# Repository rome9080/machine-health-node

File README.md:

# Industrial Machine Health Node

A 4-layer PCB that monitors the health of a machine (motor, pump, fan) by analysing vibration and motor current on-device. An FPGA running my own RISC-V CPU does the processing, and results go out over BLE, RS-485 (Modbus) or USB to a small software stack.

Full scope, parts, add-ons and phases are in [docs/PROJECT_PLAN.md](docs/PROJECT_PLAN.md). Design decisions are logged in [DESIGN_LOG.md](DESIGN_LOG.md).

## Highlights

- 4-layer board: AMD Spartan-7 FPGA (BGA), multi-rail power from a 9 to 36 V input, USB, RS-485, CAN FD
- Runs my own 32-bit RISC-V core (see [riscv-cpu](https://github.com/rome9080/riscv-cpu))
- Vibration and motor-current analysis on the device
- Add-ons: signal integrity, design for manufacture, bare-metal C toolchain, edge ML, telemetry dashboard, CI pipeline, requirements traceability

## Status

| Phase | State |
|-------|-------|
| 0. Scope and plan | Done |
| 1. Architecture and part selection | Done (final BOM costing happens in Phase 4) |
| 2. Schematic | Next |
| 3. Layout | Not started |
| 4. Fabrication | Not started |
| 5. RTL, firmware, software | Not started |
| 6. Bring-up | Not started |
| 7. Testing and write-up | Not started |

## Repository layout

- `docs/PROJECT_PLAN.md`: scope, add-ons, phases, risks
- `DESIGN_LOG.md`: decision log
- `docs/archive/`: the earlier 2-layer sensor-node concept
- Hardware, RTL, firmware and software folders will be added as each phase starts

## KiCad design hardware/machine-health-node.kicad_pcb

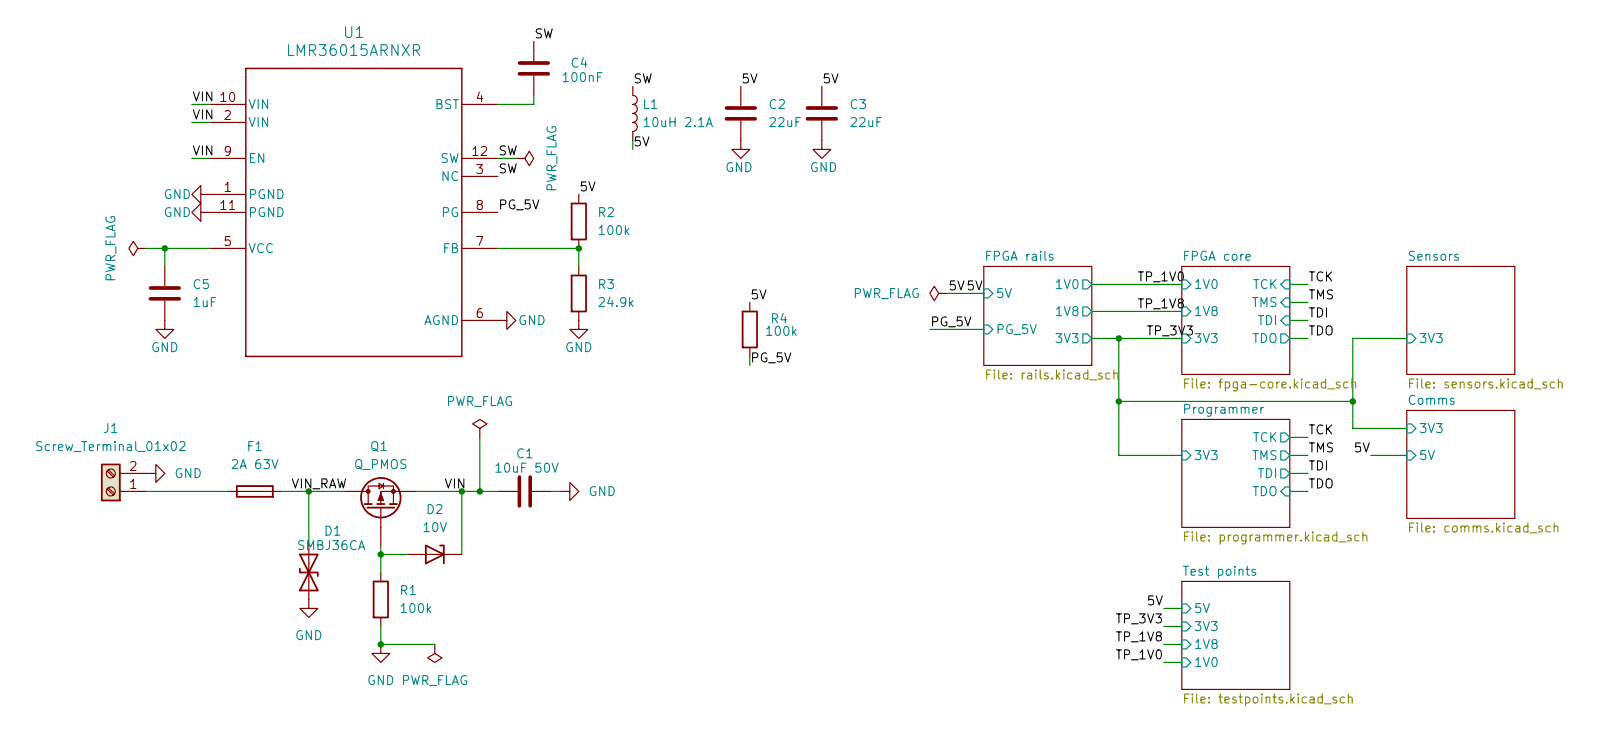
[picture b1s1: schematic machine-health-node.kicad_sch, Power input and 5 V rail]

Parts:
C1: 10uF 50V; C_1206_3216Metric
C2, C3: 22uF; C_0805_2012Metric
C4: 100nF; C_0402_1005Metric
C5: 1uF; C_0402_1005Metric
D1: SMBJ36CA; D_SMB
D2: 10V; D_SOD-123
F1: 2A 63V; Fuse_1206_3216Metric
J1: Screw_Terminal_01x02; TerminalBlock_Phoenix_MKDS-1,5-2-5.08_1x02_P5.08mm_Horizont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
L1: 10uH 2.1A; L_Taiyo-Yuden_NR-50xx
Q1: Q_PMOS; SOT-23
R1, R2, R4: 100k; R_0402_1005Metric
R3: 24.9k; R_0402_1005Metric
U1: LMR36015ARNXR; RNX0012B

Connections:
/5V: C2.1, C3.1, L1.2, R2.1, R4.1; also elsewhere on the board
/PG_5V: R4.2, U1.8 (PG); also elsewhere on the board
/SW: C4.1, L1.1, U1.3 (NC), U1.12 (SW)
/VIN: C1.1, D2.1 (K), Q1.2 (S), U1.2 (VIN), U1.9 (EN), U1.10 (VIN)
/VIN_RAW: D1.2 (A2), F1.2, Q1.3 (D)
GND: C1.2, C2.2, C3.2, C5.2, D1.1 (A1), J1.2, R1.2, R3.2, U1.1 (PGND), U1.6 (AGND), U1.11 (PGND); also elsewhere on the board
unnamed: D2.2 (A), Q1.1 (G), R1.1
unnamed: F1.1, J1.1
unnamed: C4.2, U1.4 (BST)
unnamed: R2.2, R3.1, U1.7 (FB)
unnamed: C5.1, U1.5 (VCC)

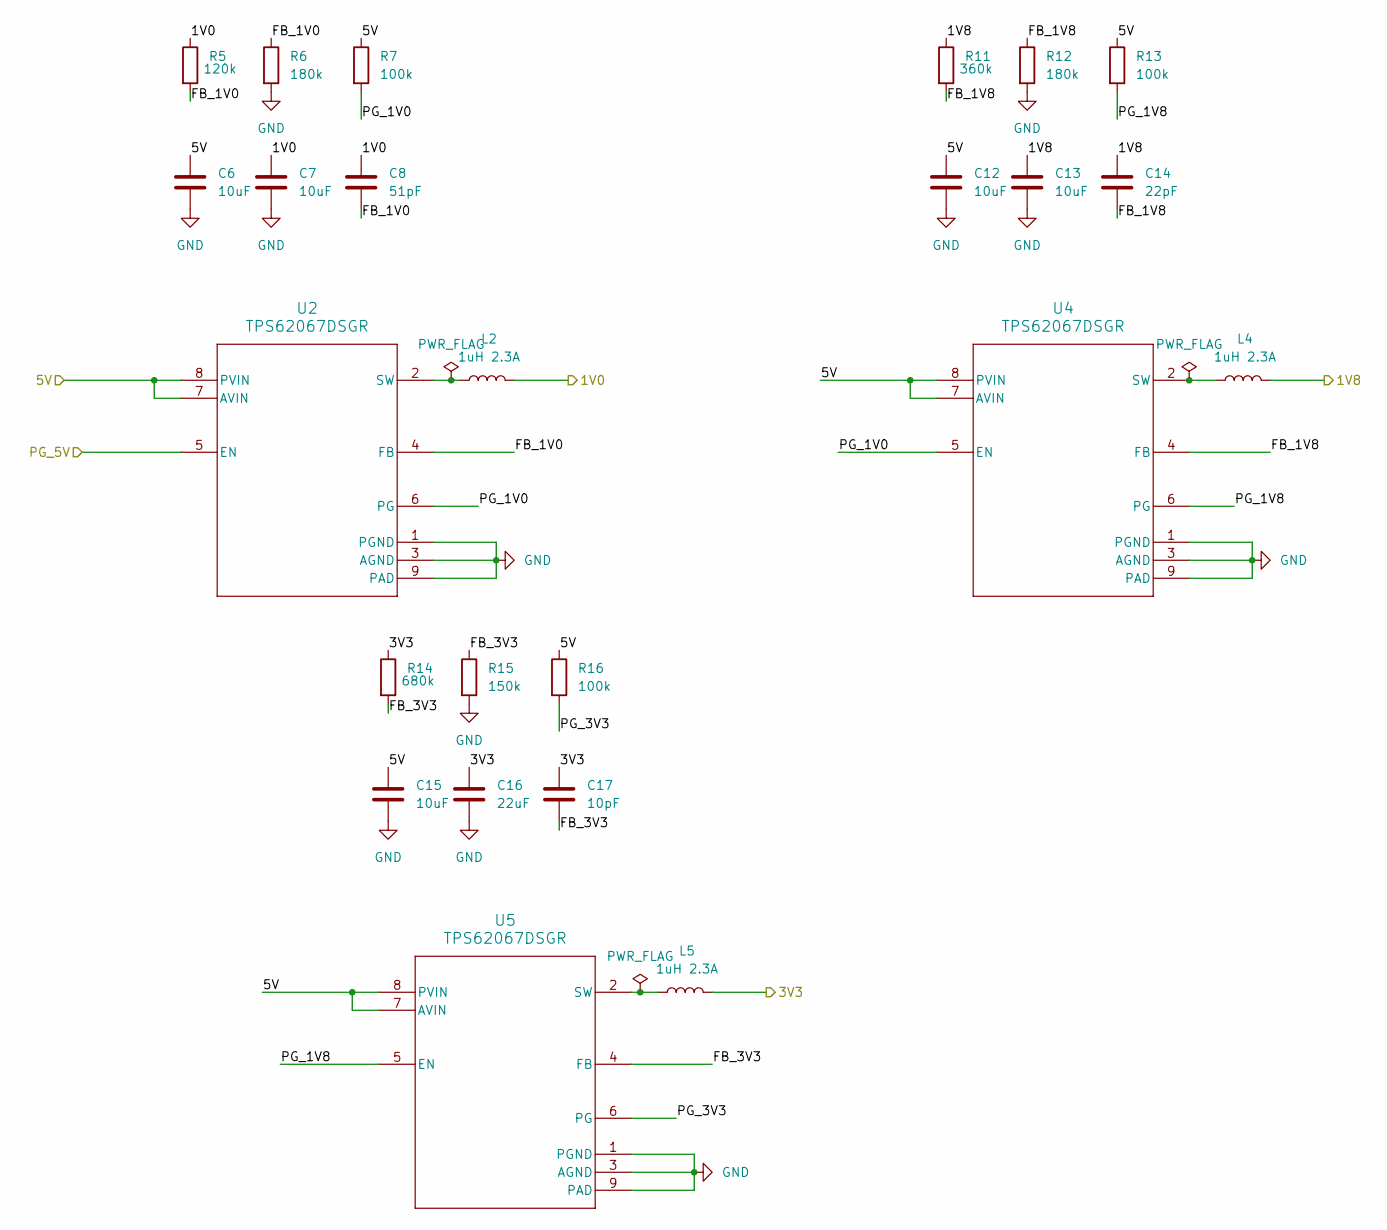
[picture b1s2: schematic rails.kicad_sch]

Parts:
C6, C7, C12, C13, C15: 10uF; C_0805_2012Metric
C8: 51pF; C_0402_1005Metric
C14: 22pF; C_0402_1005Metric
C16: 22uF; C_0805_2012Metric
C17: 10pF; C_0402_1005Metric
L2, L4, L5: 1uH 2.3A; L_Taiyo-Yuden_NR-30xx
R5: 120k; R_0402_1005Metric
R6, R12: 180k; R_0402_1005Metric
R7, R13, R16: 100k; R_0402_1005Metric
R11: 360k; R_0402_1005Metric
R14: 680k; R_0402_1005Metric
R15: 150k; R_0402_1005Metric
U2, U4, U5: TPS62067DSGR; DSG0008A

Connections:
/5V: C6.1, C12.1, C15.1, R7.1, R13.1, R16.1, U2.7 (AVIN), U2.8 (PVIN), U4.7 (AVIN), U4.8 (PVIN), U5.7 (AVIN), U5.8 (PVIN); also elsewhere on the board
/FPGA rails/FB_1V0: C8.2, R5.2, R6.1, U2.4 (FB)
/FPGA rails/FB_1V8: C14.2, R11.2, R12.1, U4.4 (FB)
/FPGA rails/FB_3V3: C17.2, R14.2, R15.1, U5.4 (FB)
/FPGA rails/PG_1V0: R7.2, U2.6 (PG), U4.5 (EN)
/FPGA rails/PG_1V8: R13.2, U4.6 (PG), U5.5 (EN)
/FPGA rails/PG_3V3: R16.2, U5.6 (PG)
/PG_5V: U2.5 (EN); also elsewhere on the board
/TP_1V0: C7.1, C8.1, L2.2, R5.1; also elsewhere on the board
/TP_1V8: C13.1, C14.1, L4.2, R11.1; also elsewhere on the board
/TP_3V3: C16.1, C17.1, L5.2, R14.1; also elsewhere on the board
GND: C6.2, C7.2, C12.2, C13.2, C15.2, C16.2, R6.2, R12.2, R15.2, U2.1 (PGND), U2.3 (AGND), U2.9 (PAD), U4.1 (PGND), U4.3 (AGND), U4.9 (PAD), U5.1 (PGND), U5.3 (AGND), U5.9 (PAD); also elsewhere on the board
unnamed: L2.1, U2.2 (SW)
unnamed: L4.1, U4.2 (SW)
unnamed: L5.1, U5.2 (SW)

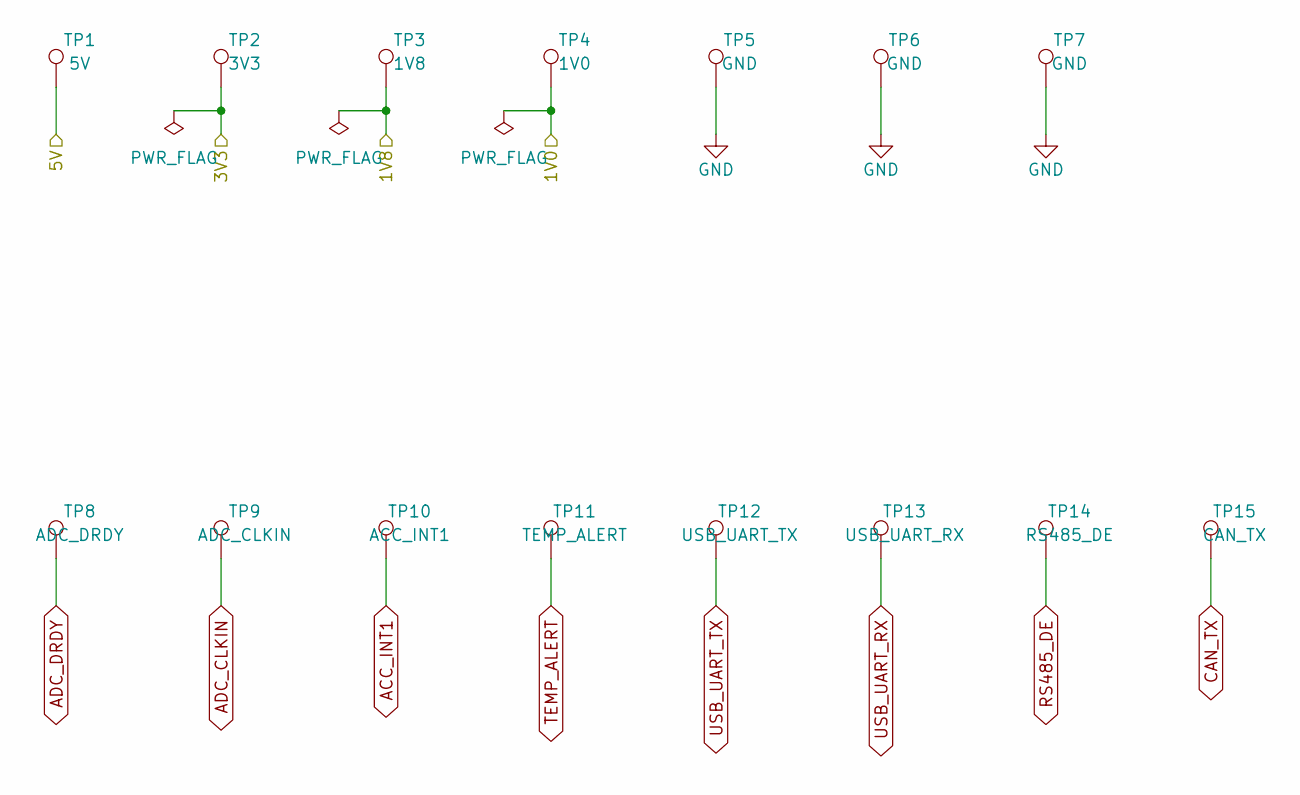
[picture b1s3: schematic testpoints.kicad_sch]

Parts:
TP1: 5V; TestPoint_Pad_D1.0mm
TP2: 3V3; TestPoint_Pad_D1.0mm
TP3: 1V8; TestPoint_Pad_D1.0mm
TP4: 1V0; TestPoint_Pad_D1.0mm
TP5, TP6, TP7: GND; TestPoint_Pad_D1.0mm
TP8: ADC_DRDY; TestPoint_Pad_D1.0mm
TP9: ADC_CLKIN; TestPoint_Pad_D1.0mm
TP10: ACC_INT1; TestPoint_Pad_D1.0mm
TP11: TEMP_ALERT; TestPoint_Pad_D1.0mm
TP12: USB_UART_TX; TestPoint_Pad_D1.0mm
TP13: USB_UART_RX; TestPoint_Pad_D1.0mm
TP14: RS485_DE; TestPoint_Pad_D1.0mm
TP15: CAN_TX; TestPoint_Pad_D1.0mm

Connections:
/5V: TP1.1 (1_1); also elsewhere on the board
/TP_1V0: TP4.1 (1_1); also elsewhere on the board
/TP_1V8: TP3.1 (1_1); also elsewhere on the board
/TP_3V3: TP2.1 (1_1); also elsewhere on the board
ACC_INT1: TP10.1 (1_1); also elsewhere on the board
ADC_CLKIN: TP9.1 (1_1); also elsewhere on the board
ADC_DRDY: TP8.1 (1_1); also elsewhere on the board
CAN_TX: TP15.1 (1_1); also elsewhere on the board
GND: TP5.1 (1_1), TP6.1 (1_1), TP7.1 (1_1); also elsewhere on the board
RS485_DE: TP14.1 (1_1); also elsewhere on the board
TEMP_ALERT: TP11.1 (1_1); also elsewhere on the board
USB_UART_RX: TP13.1 (1_1); also elsewhere on the board
USB_UART_TX: TP12.1 (1_1); also elsewhere on the board

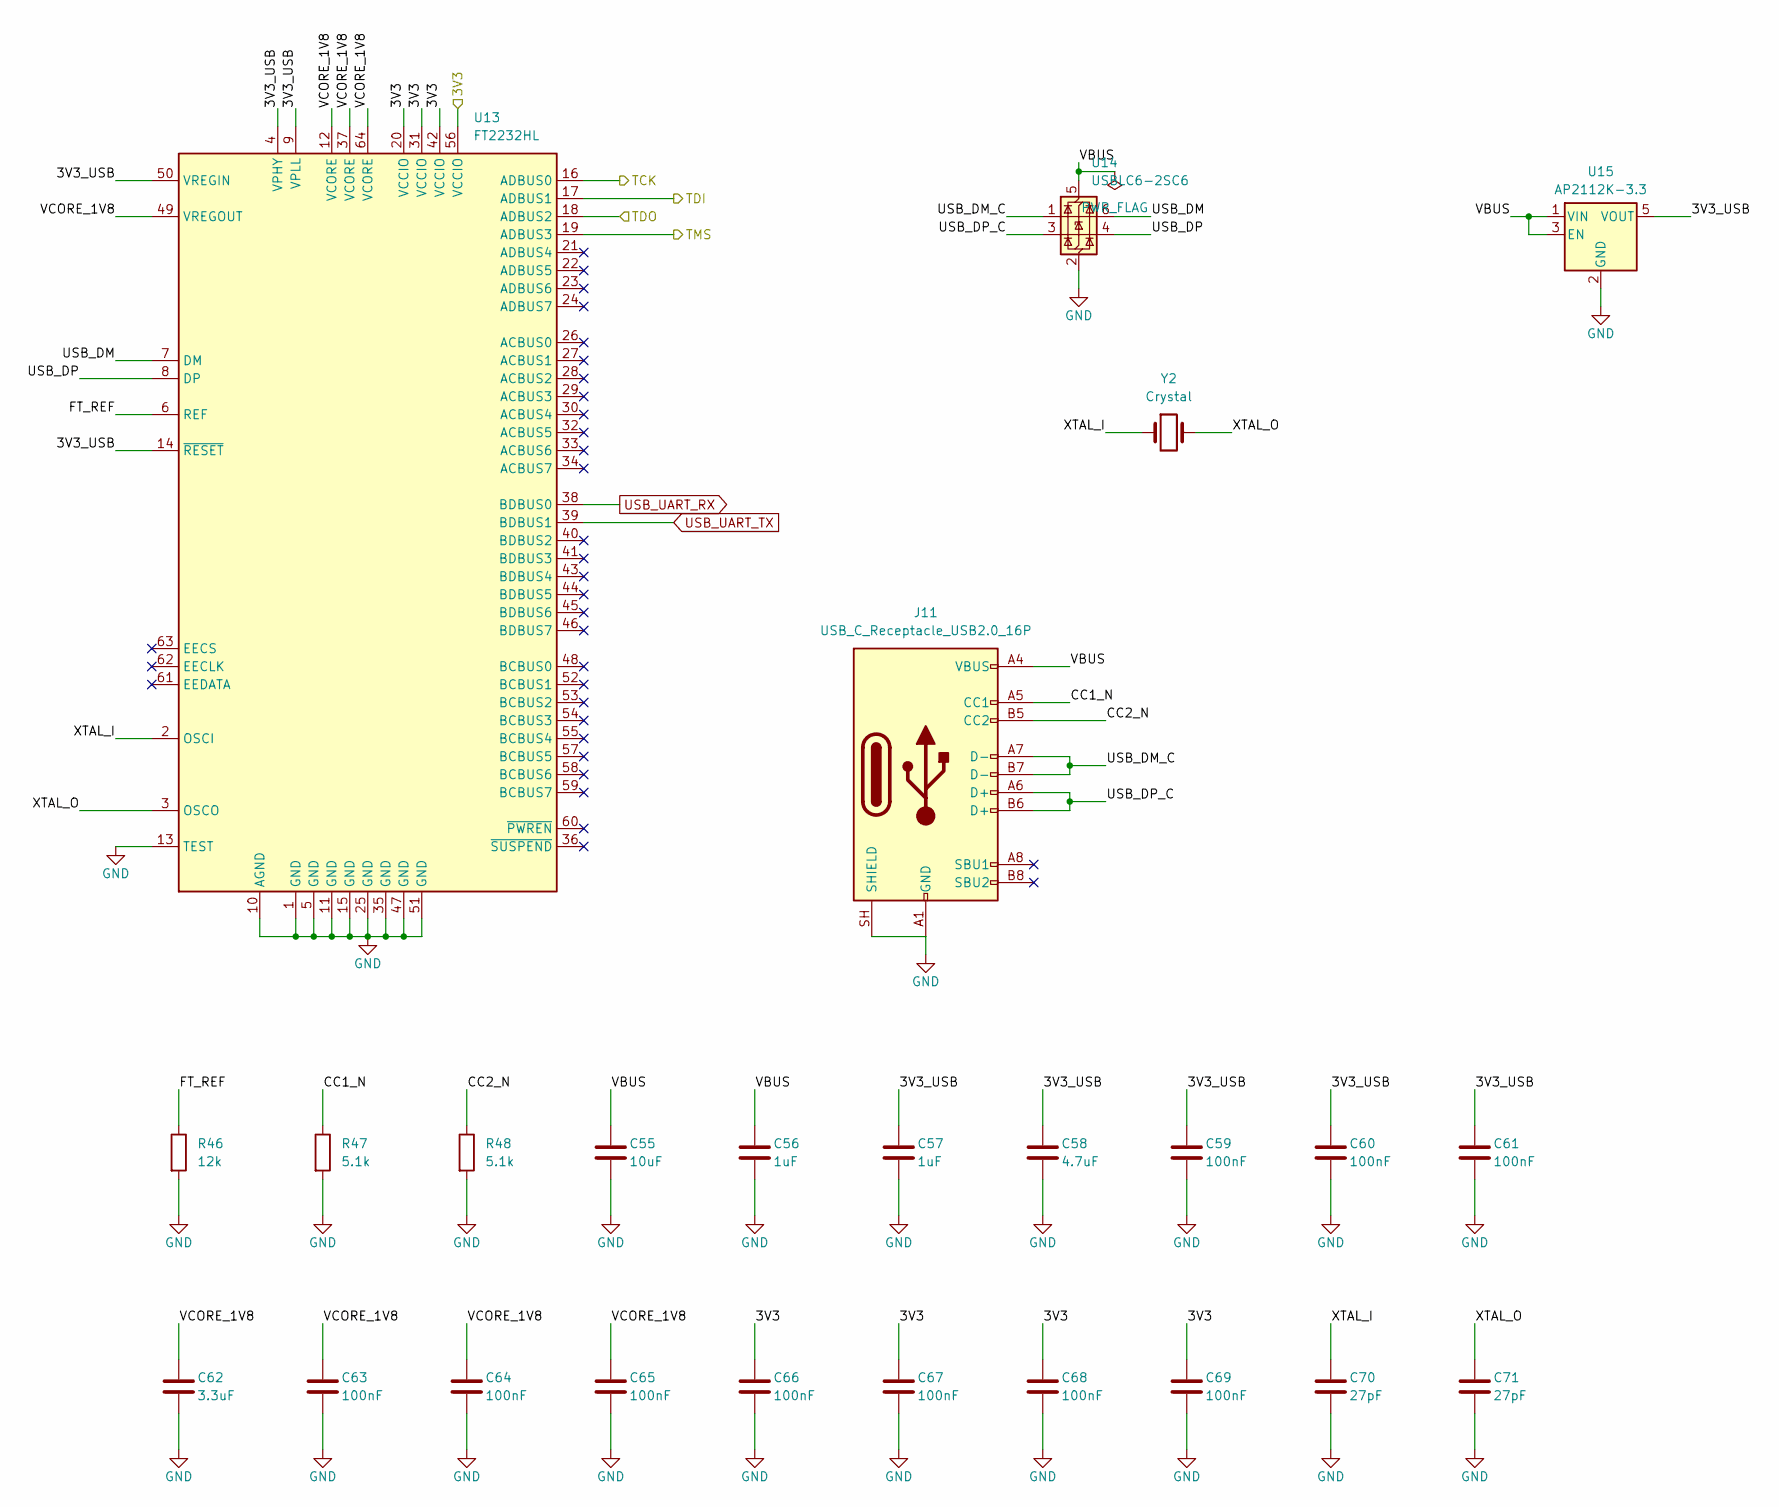
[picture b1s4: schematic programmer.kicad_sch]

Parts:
C55: 10uF; C_0805_2012Metric
C56, C57: 1uF; C_0402_1005Metric
C58: 4.7uF; C_0603_1608Metric
C59, C60, C61, C63, C64, C65, C66, C67, C68, C69: 100nF; C_0402_1005Metric
C62: 3.3uF; C_0603_1608Metric
C70, C71: 27pF; C_0402_1005Metric
J11: USB_C_Receptacle_USB2.0_16P; USB_C_Receptacle_GCT_USB4105-xx-A_16P_TopMnt_Horizontal
R46: 12k; R_0402_1005Metric
R47, R48: 5.1k; R_0402_1005Metric
U13: FT2232HL; LQFP-64_10x10mm_P0.5mm
U14: USBLC6-2SC6; SOT-23-6
U15: AP2112K-3.3; SOT-23-5
Y2: Crystal; Crystal_SMD_5032-2Pin_5.0x3.2mm

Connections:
/Programmer/3V3_USB: C57.1, C58.1, C59.1, C60.1, C61.1, U13.4 (VPHY), U13.9 (VPLL), U13.14 (~RESET), U13.50 (VREGIN), U15.5 (VOUT)
/Programmer/CC1_N: J11.A5 (CC1), R47.1
/Programmer/CC2_N: J11.B5 (CC2), R48.1
/Programmer/FT_REF: R46.1, U13.6 (REF)
/Programmer/USB_DM: U13.7 (DM), U14.6 (I/O1)
/Programmer/USB_DM_C: J11.A7 (D-), J11.B7 (D-), U14.1 (I/O1)
/Programmer/USB_DP: U13.8 (DP), U14.4 (I/O2)
/Programmer/USB_DP_C: J11.A6 (D+), J11.B6 (D+), U14.3 (I/O2)
/Programmer/VBUS: C55.1, C56.1, J11.A4 (VBUS), J11.A9 (VBUS), J11.B4 (VBUS), J11.B9 (VBUS), U14.5 (VBUS), U15.1 (VIN), U15.3 (EN)
/Programmer/VCORE_1V8: C62.1, C63.1, C64.1, C65.1, U13.12 (VCORE), U13.37 (VCORE), U13.49 (VREGOUT), U13.64 (VCORE)
/Programmer/XTAL_I: C70.1, U13.2 (OSCI), Y2.1
/Programmer/XTAL_O: C71.1, U13.3 (OSCO), Y2.2
/TCK: U13.16 (ADBUS0); also elsewhere on the board
/TDI: U13.17 (ADBUS1); also elsewhere on the board
/TDO: U13.18 (ADBUS2); also elsewhere on the board
/TMS: U13.19 (ADBUS3); also elsewhere on the board
/TP_3V3: C66.1, C67.1, C68.1, C69.1, U13.20 (VCCIO), U13.31 (VCCIO), U13.42 (VCCIO), U13.56 (VCCIO); also elsewhere on the board
GND: C55.2, C56.2, C57.2, C58.2, C59.2, C60.2, C61.2, C62.2, C63.2, C64.2, C65.2, C66.2, C67.2, C68.2, C69.2, C70.2, C71.2, J11.A1 (GND), J11.A12 (GND), J11.B1 (GND), J11.B12 (GND), J11.SH (SHIELD), R46.2, R47.2, R48.2, U13.1 (GND), U13.5 (GND), U13.10 (AGND), U13.11 (GND), U13.13 (TEST), U13.15 (GND), U13.25 (GND), U13.35 (GND), U13.47 (GND), U13.51 (GND), U14.2 (GND), U15.2 (GND); also elsewhere on the board
USB_UART_RX: U13.38 (BDBUS0); also elsewhere on the board
USB_UART_TX: U13.39 (BDBUS1); also elsewhere on the board

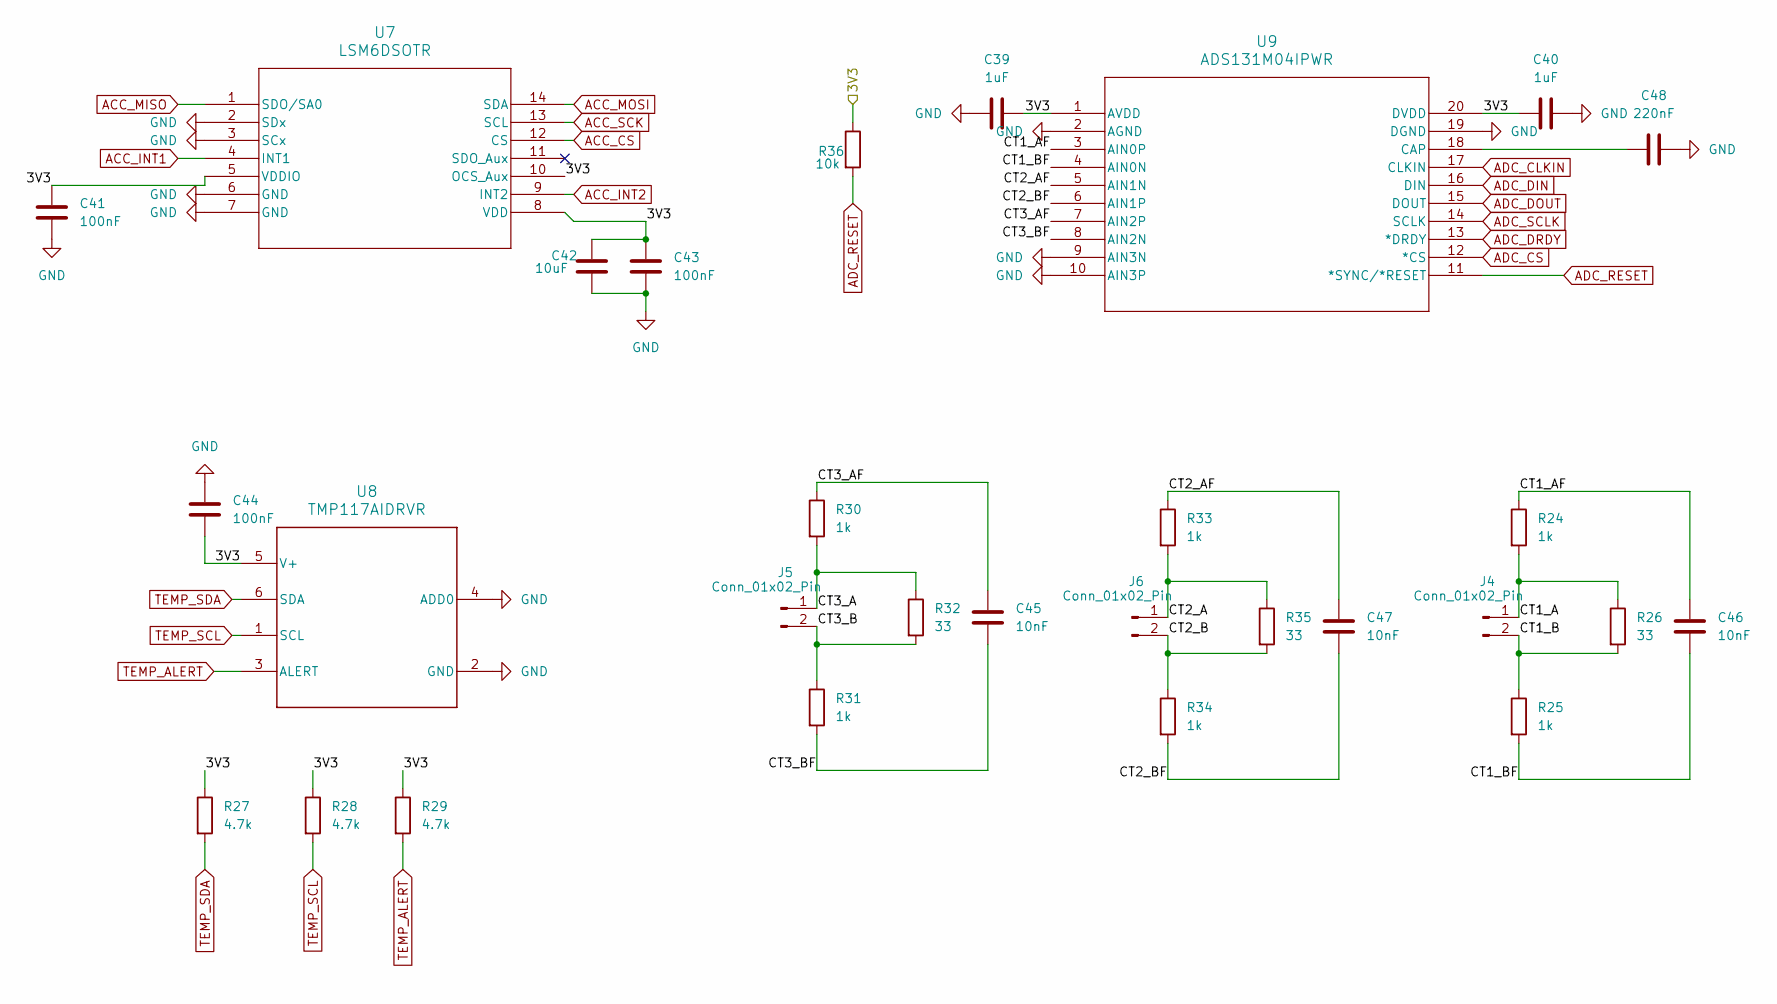
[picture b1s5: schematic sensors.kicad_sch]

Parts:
C39, C40: 1uF; C_0402_1005Metric
C41, C43, C44: 100nF; C_0402_1005Metric
C42: 10uF; C_0805_2012Metric
C45, C46, C47: 10nF; C_0402_1005Metric
C48: 220nF; C_0402_1005Metric
J4, J5, J6: Conn_01x02_Pin; PinHeader_1x02_P2.54mm_Vertical
R24, R25, R30, R31, R33, R34: 1k; R_0402_1005Metric
R26, R32, R35: 33; R_0402_1005Metric
R27, R28, R29: 4.7k; R_0402_1005Metric
R36: 10k; R_0402_1005Metric
U7: LSM6DSOTR; LGA-14L_2P5X3X0P86_STM
U8: TMP117AIDRVR; DRV0006B
U9: ADS131M04IPWR; PW20_TEX

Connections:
/Sensors/CT1_A: J4.1, R24.2, R26.1
/Sensors/CT1_AF: C46.1, R24.1, U9.3 (AIN0P)
/Sensors/CT1_B: J4.2, R25.1, R26.2
/Sensors/CT1_BF: C46.2, R25.2, U9.4 (AIN0N)
/Sensors/CT2_A: J6.1, R33.2, R35.1
/Sensors/CT2_AF: C47.1, R33.1, U9.5 (AIN1N)
/Sensors/CT2_B: J6.2, R34.1, R35.2
/Sensors/CT2_BF: C47.2, R34.2, U9.6 (AIN1P)
/Sensors/CT3_A: J5.1, R30.2, R32.1
/Sensors/CT3_AF: C45.1, R30.1, U9.7 (AIN2P)
/Sensors/CT3_B: J5.2, R31.1, R32.2
/Sensors/CT3_BF: C45.2, R31.2, U9.8 (AIN2N)
/TP_3V3: C39.2, C40.1, C41.1, C42.1, C43.1, C44.2, R27.1, R28.1, R29.1, R36.1, U7.5 (VDDIO), U7.8 (VDD), U7.10 (OCS_Aux), U8.5 (V+), U9.1 (AVDD), U9.20 (DVDD); also elsewhere on the board
ACC_CS: U7.12 (CS); also elsewhere on the board
ACC_INT1: U7.4 (INT1); also elsewhere on the board
ACC_INT2: U7.9 (INT2); also elsewhere on the board
ACC_MISO: U7.1 (SDO/SA0); also elsewhere on the board
ACC_MOSI: U7.14 (SDA); also elsewhere on the board
ACC_SCK: U7.13 (SCL); also elsewhere on the board
ADC_CLKIN: U9.17 (CLKIN); also elsewhere on the board
ADC_CS: U9.12 (*CS); also elsewhere on the board
ADC_DIN: U9.16 (DIN); also elsewhere on the board
ADC_DOUT: U9.15 (DOUT); also elsewhere on the board
ADC_DRDY: U9.13 (*DRDY); also elsewhere on the board
ADC_RESET: R36.2, U9.11 (*SYNC/*RESET); also elsewhere on the board
ADC_SCLK: U9.14 (SCLK); also elsewhere on the board
GND: C39.1, C40.2, C41.2, C42.2, C43.2, C44.1, C48.2, U7.2 (SDx), U7.3 (SCx), U7.6 (GND), U7.7 (GND), U8.2 (GND), U8.4 (ADD0), U9.2 (AGND), U9.9 (AIN3N), U9.10 (AIN3P), U9.19 (DGND); also elsewhere on the board
unnamed: C48.1, U9.18 (CAP)
TEMP_ALERT: R29.2, U8.3 (ALERT); also elsewhere on the board
TEMP_SCL: R28.2, U8.1 (SCL); also elsewhere on the board
TEMP_SDA: R27.2, U8.6 (SDA); also elsewhere on the board

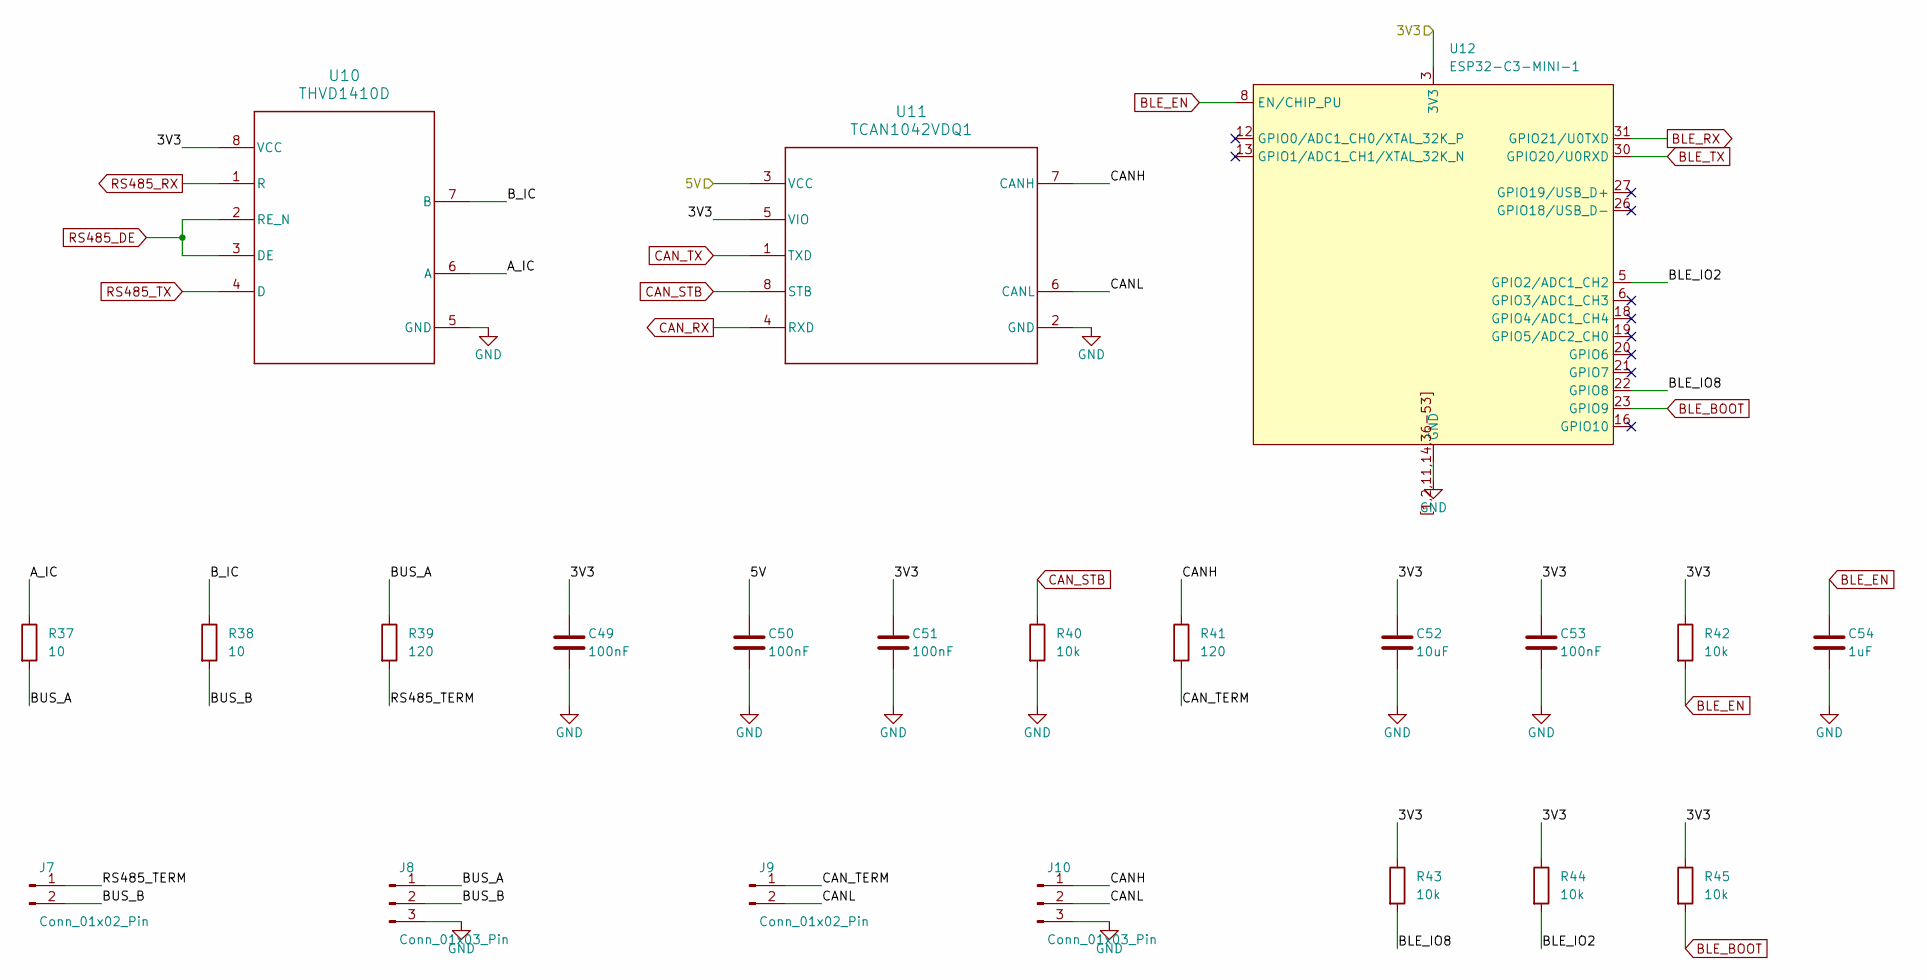
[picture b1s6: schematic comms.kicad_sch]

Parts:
C49, C50, C51, C53: 100nF; C_0402_1005Metric
C52: 10uF; C_0805_2012Metric
C54: 1uF; C_0402_1005Metric
J7, J9: Conn_01x02_Pin; PinHeader_1x02_P2.54mm_Vertical
J8, J10: Conn_01x03_Pin; PinHeader_1x03_P2.54mm_Vertical
R37, R38: 10; R_0402_1005Metric
R39, R41: 120; R_0402_1005Metric
R40, R42, R43, R44, R45: 10k; R_0402_1005Metric
U10: THVD1410D; D0008A_N
U11: TCAN1042VDQ1; D0008A_N
U12: ESP32-C3-MINI-1

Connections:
/5V: C50.1, U11.3 (VCC); also elsewhere on the board
/Comms/A_IC: R37.1, U10.6 (A)
/Comms/BLE_IO2: R44.2, U12.5 (GPIO2/ADC1_CH2)
/Comms/BLE_IO8: R43.2, U12.22 (GPIO8)
/Comms/BUS_A: J8.1, R37.2, R39.1
/Comms/BUS_B: J7.2, J8.2, R38.2
/Comms/B_IC: R38.1, U10.7 (B)
/Comms/CANH: J10.1, R41.1, U11.7 (CANH)
/Comms/CANL: J9.2, J10.2, U11.6 (CANL)
/Comms/CAN_TERM: J9.1, R41.2
/Comms/RS485_TERM: J7.1, R39.2
/TP_3V3: C49.1, C51.1, C52.1, C53.1, R42.1, R43.1, R44.1, R45.1, U10.8 (VCC), U11.5 (VIO), U12.3 (3V3); also elsewhere on the board
BLE_BOOT: R45.2, U12.23 (GPIO9); also elsewhere on the board
BLE_EN: C54.1, R42.2, U12.8 (EN/CHIP_PU); also elsewhere on the board
BLE_RX: U12.31 (GPIO21/U0TXD); also elsewhere on the board
BLE_TX: U12.30 (GPIO20/U0RXD); also elsewhere on the board
CAN_RX: U11.4 (RXD); also elsewhere on the board
CAN_STB: R40.1, U11.8 (STB); also elsewhere on the board
CAN_TX: U11.1 (TXD); also elsewhere on the board
GND: C49.2, C50.2, C51.2, C52.2, C53.2, C54.2, J8.3, J10.3, R40.2, U10.5 (GND), U11.2 (GND), U12.1 (GND), U12.2 (GND), U12.11 (GND), U12.14 (GND), U12.36 (GND), U12.37 (GND), U12.38 (GND), U12.39 (GND), U12.40 (GND), U12.41 (GND), U12.42 (GND), U12.43 (GND), U12.44 (GND), U12.45 (GND), U12.46 (GND), U12.47 (GND), U12.48 (GND), U12.49 (GND), U12.50 (GND), U12.51 (GND), U12.52 (GND), U12.53 (GND), U12.[1,2,11,14,36-53] (GND); also elsewhere on the board
RS485_DE: U10.2 (RE_N), U10.3 (DE); also elsewhere on the board
RS485_RX: U10.1 (R); also elsewhere on the board
RS485_TX: U10.4 (D); also elsewhere on the board
